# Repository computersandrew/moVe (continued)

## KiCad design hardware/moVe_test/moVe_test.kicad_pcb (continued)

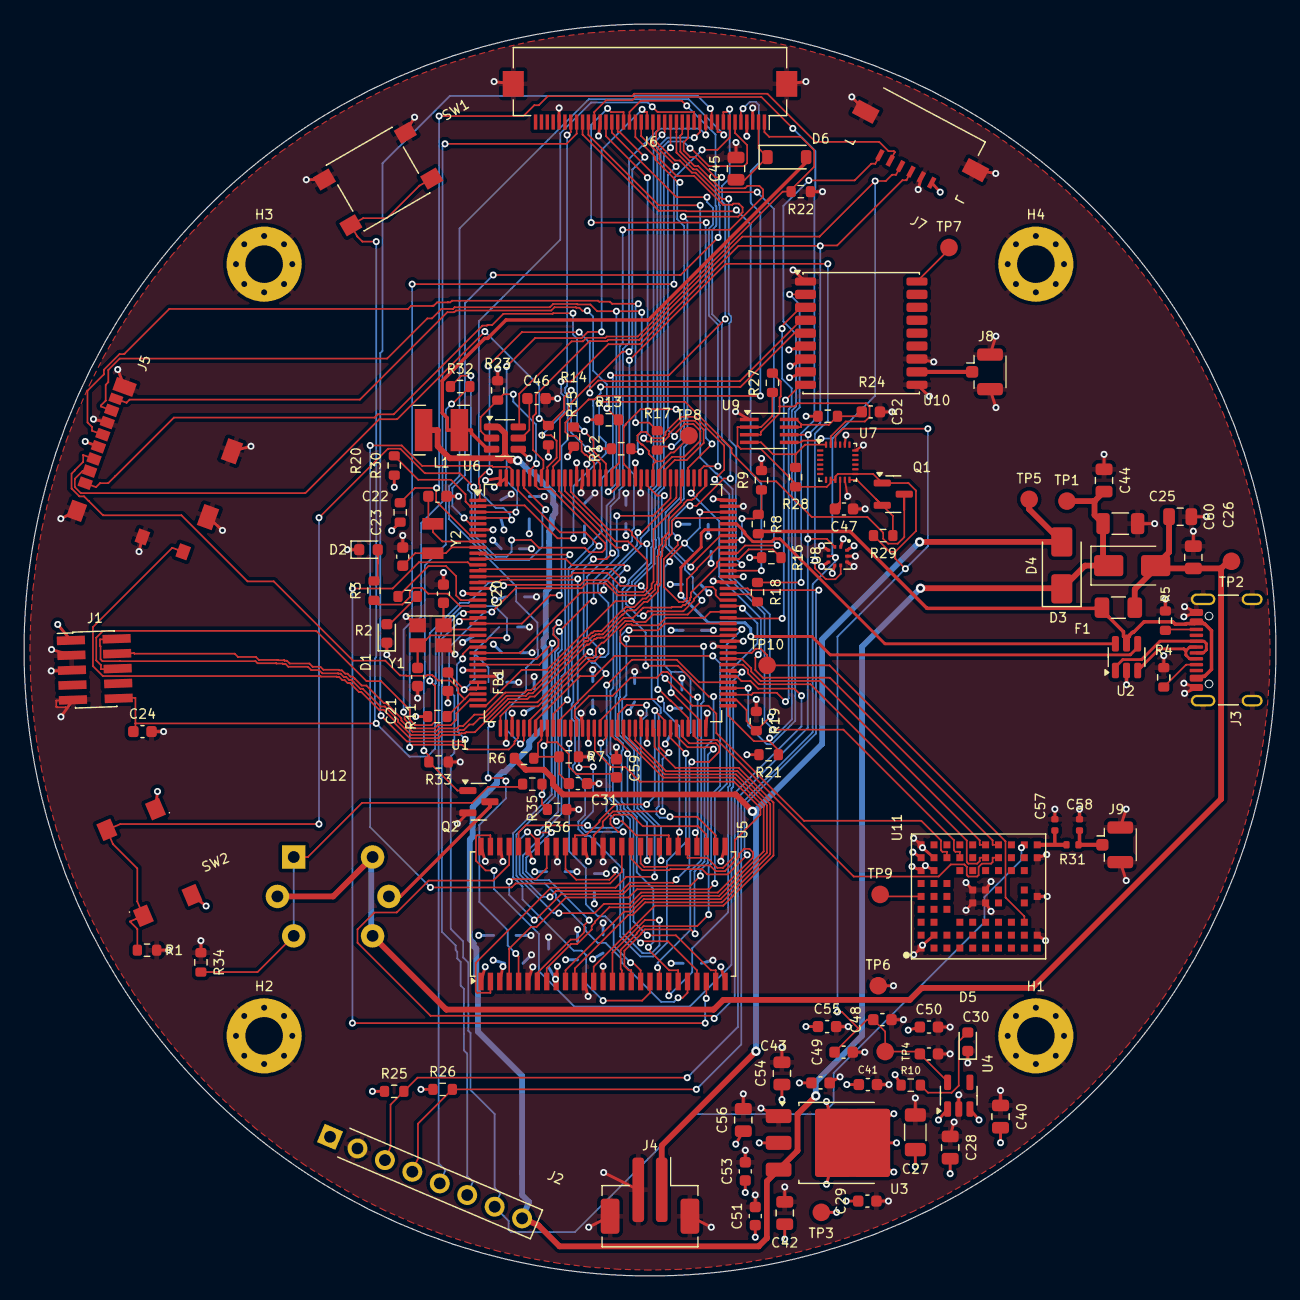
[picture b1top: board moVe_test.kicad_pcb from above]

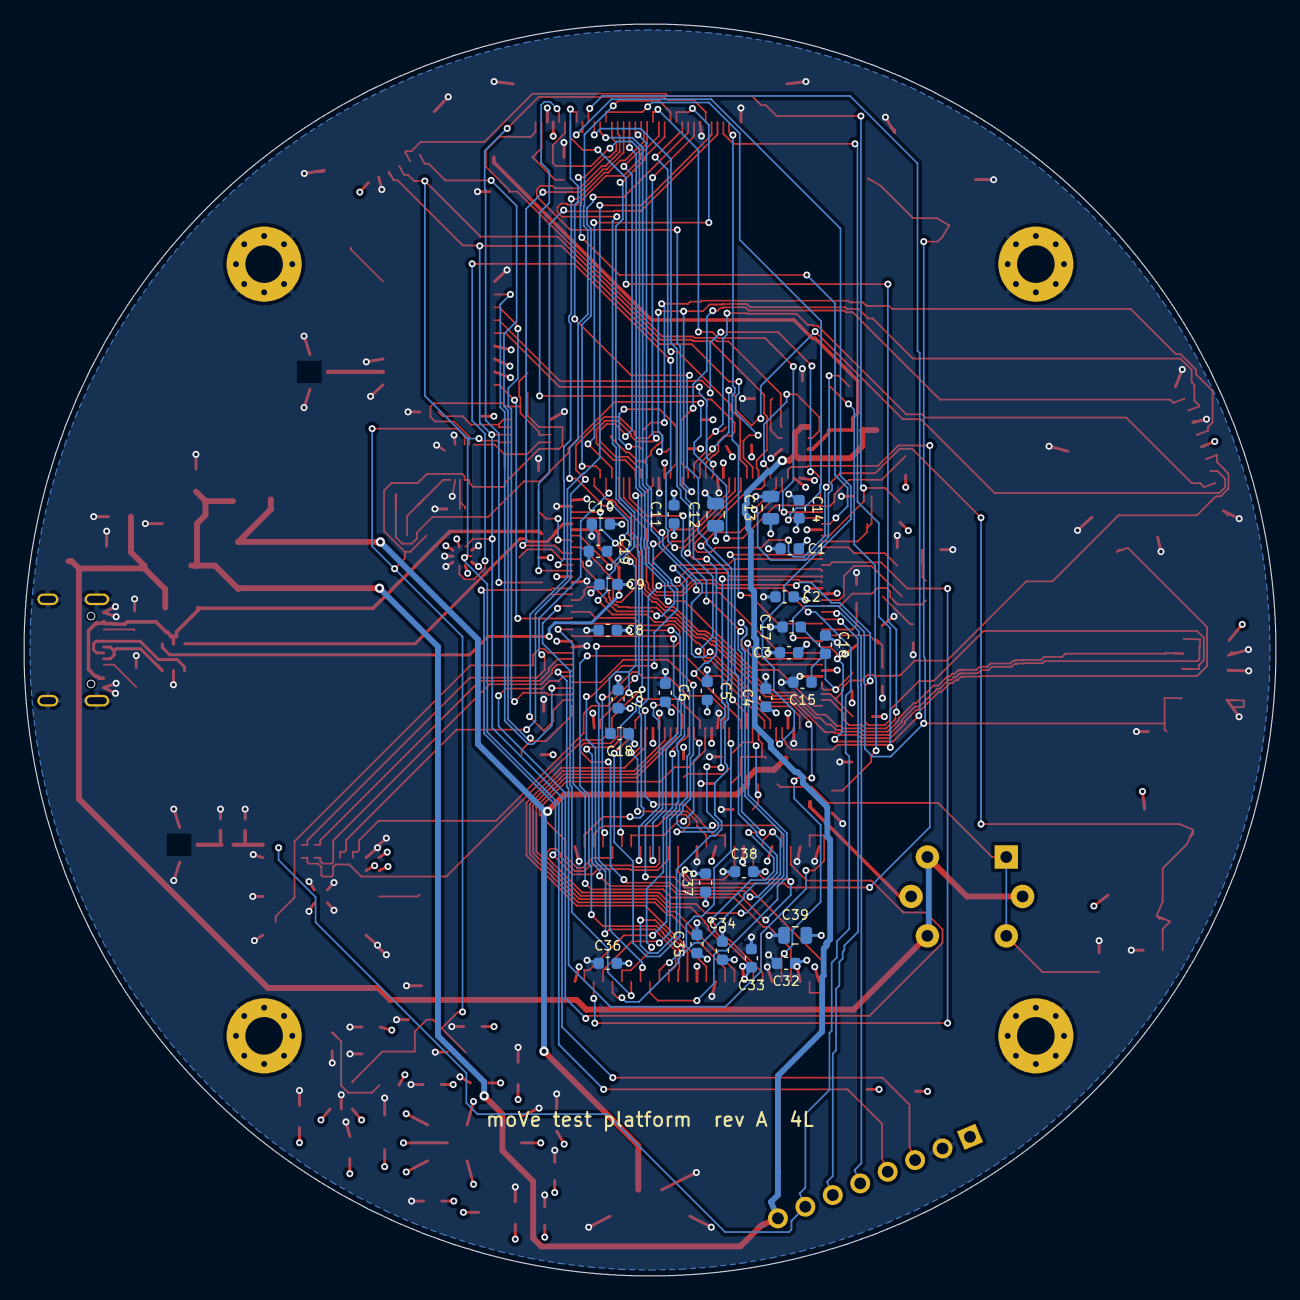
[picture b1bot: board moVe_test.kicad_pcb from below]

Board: 4 copper layers, 106.7 x 106.7 mm, 146 parts (27 on the bottom side), 149 nets.

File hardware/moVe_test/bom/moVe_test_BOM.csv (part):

Ref,Description,Qty per board,Unit price (USD),Per board (USD),MPN,Manufacturer,Category,Price basis,Link
U1,"MCU, Cortex-M7 550 MHz, LQFP-144",1,11.69,11.69,STM32H723ZGT6,STMicroelectronics,IC,parts.csv (Apr 2026),https://www.digikey.com/en/products/result?keywords=STM32H723ZGT6
U5,"64 Mb SDRAM x16, TSOP-II-54",1,3.13,3.13,AS4C4M16SA-7TCN,Alliance Memory,IC,parts.csv (Apr 2026),https://www.digikey.com/en/products/result?keywords=AS4C4M16SA-7TCN
U10,GNSS module,1,13.33,13.33,MAX-M10S-00B,u-blox,Module,parts.csv (Apr 2026),https://www.digikey.com/en/products/result?keywords=MAX-M10S-00B
U11,Bluetooth LE module,1,9.13,9.13,NORA-B261-00B,u-blox,Module,parts.csv (Apr 2026),https://www.digikey.com/en/products/result?keywords=NORA-B261-00B
U7,9-axis IMU,1,6.78,6.78,ICM-20948,TDK InvenSense,IC,parts.csv (Apr 2026),https://www.digikey.com/en/products/result?keywords=ICM-20948
U8,Barometric pressure sensor,1,3.15,3.15,BMP390,Bosch,IC,parts.csv (Apr 2026),https://www.digikey.com/en/products/result?keywords=BMP390
U12,CO gas sensor (aircraft build only),1,7.50,7.50,MQ-7B,Winsen,Sensor,parts.csv (Apr 2026),https://www.digikey.com/en/products/result?keywords=MQ-7B
U6,WLED backlight boost driver,1,2.15,2.15,TPS61165DBVR,Texas Instruments,IC,parts.csv (Apr 2026),https://www.digikey.com/en/products/result?keywords=TPS61165DBVR
U3,"3.3 V LDO, 800 mA, TO-252",1,0.96,0.96,TLV1117-33IKVURG3,Texas Instruments,IC,parts.csv (Apr 2026),https://www.digikey.com/en/products/result?keywords=TLV1117-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
U4,"1.8 V LDO, SOT-23-5",1,0.22,0.22,AP2112K-1.8TRG1,Diodes Inc.,IC,parts.csv (Apr 2026),https://www.digikey.com/en/products/result?keywords=AP2112K-1.8TRG1
U9,I2C level translator,1,0.69,0.69,PCA9306DCTR,Texas Instruments,IC,parts.csv (Apr 2026),https://www.digikey.com/en/products/result?keywords=PCA9306DCTR
U2,"USB ESD protection, SOT-23-6",1,0.36,0.36,USBLC6-2SC6,STMicroelectronics,IC,DigiKey US 1-pc (Nov 2026),https://www.digikey.com/en/products/result?keywords=USBLC6-2SC6
Q1,"N-MOSFET, SOT-23",1,0.20,0.20,BSS138,onsemi,Discrete,Est.,https://www.digikey.com/en/products/result?keywords=BSS138
Q2,"N-MOSFET, SOT-23 (MQ-7 heater)",1,0.30,0.30,AO3400A,Alpha & Omega,Discrete,Est.,https://www.digikey.com/en/products/result?keywords=AO3400A
Y1,"Crystal 25 MHz, 3225",1,0.65,0.65,ABM8-25.000MHZ-B2-T,Abracon,Discrete,"Farnell UK 1+ (£0.50, converted)",https://www.digikey.com/en/products/result?keywords=ABM8-25.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
Y2,"Crystal 32.768 kHz, 3215",1,0.59,0.59,ABS07-32.768KHZ-7-T,Abracon,Discrete,LCSC 1+ (Nov 2026),https://www.digikey.com/en/products/result?keywords=ABS07-32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
F1,"PTC fuse 1.1 A hold, 1812",1,0.37,0.37,MF-MSMF110-2,Bourns,Discrete,Findchips 1-pc (Nov 2026),https://www.digikey.com/en/products/result?keywords=MF-MSMF110-2
"D3,D4","Schottky 3 A 40 V, SMA",2,0.15,0.30,SS34,Generic,Discrete,Est.,https://www.digikey.com/en/products/result?keywords=SS34
D6,"Schottky 0.5 A 40 V, SOD-123",1,0.20,0.20,B0540W-7-F,Diodes Inc.,Discrete,Est.,https://www.digikey.com/en/products/result?keywords=B0540W-7-F
L1,"Power inductor 10 µH, 4018",1,0.37,0.37,SRN4018-100M,Bourns,Discrete,LCSC 1+ (Nov 2026),https://www.digikey.com/en/products/result?keywords=SRN4018-100M
FB1,"Ferrite bead 600 Ω @100 MHz, 0603",1,0.10,0.10,BLM18PG601SN1D,Murata,Discrete,Est.,https://www.digikey.com/en/products/result?keywords=BLM18PG601SN1D
D1,"LED green, 0603",1,0.10,0.10,,Generic,Discrete,Est.,https://www.digikey.com/en/products/result?keywords=LED+green+0603
D2,"LED blue, 0603",1,0.10,0.10,,Generic,Discrete,Est.,https://www.digikey.com/en/products/result?keywords=LED+blue+0603
D5,"LED red, 0603",1,0.10,0.10,,Generic,Discrete,Est.,https://www.digikey.com/en/products/result?keywords=LED+red+0603
J1,SWD header 2x5 1.27 mm,1,2.81,2.81,FTSH-105-01-L-DV-K-P,Samtec,Connector,parts.csv (Apr 2026),https://www.digikey.com/en/products/result?keywords=FTSH-105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
J2,Expansion header 1x8 2.54 mm,1,0.50,0.50,,Generic,Connector,Est.,https://www.digikey.com/en/products/result?keywords=1x8+pin+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
J3,USB-C receptacle,1,0.78,0.78,USB4105-GF-A-120,GCT,Connector,parts.csv (Apr 2026),https://www.digikey.com/en/products/result?keywords=USB4105-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
J4,Battery connector JST PH 2-pin SMD,1,0.43,0.43,B2B-PH-SM4-TB(LF)(SN),JST,Connector,LCSC 1+ (Nov 2026),https://www.digikey.com/en/products/result?keywords=B2B-PH-S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
J5,microSD socket,1,2.04,2.04,1040310811,Molex,Connector,parts.csv (Apr 2026),https://www.digikey.com/en/products/result?keywords=1040310811
J6,Display FPC 40-pin 0.5 mm,1,0.66,0.66,FH12-40S-0.5SH(55),Hirose,Connector,LCSC 1+ (Nov 2026),https://www.digikey.com/en/products/result?keywords=FH12-40S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
J7,Touch FFC 6-pin 1.0 mm,1,0.48,0.48,2005280060,Molex,Connector,TME 1+ (Nov 2026),https://www.digikey.com/en/products/result?keywords=2005280060
"J8,J9",U.FL antenna connector,2,1.20,2.40,U.FL-R-SMT-1(10),Hirose,Connector,parts.csv (Apr 2026),https://www.digikey.com/en/products/result?keywords=U.FL-R-S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
"SW1,SW2","Tactile switch (RESET, BOOT0)",2,0.32,0.64,PTS645SK43SMTR92 LFS,C&K,Connector,parts.csv (Apr 2026),https://www.digikey.com/en/products/result?keywords=PTS645SK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
"C1-C11,C14,C16,C17,C24,C31-C38,C41,C43,C47-C53,C55,C59","Cap 100 nF, 0603",34,0.02,0.68,,Generic,Passive,"Est. generic, 10+ cut tape",https://www.digikey.com/en/products/result?keywords=capacito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
"C12,C13,C44","Cap 4.7 µF, 0805",3,0.08,0.24,,Generic,Passive,"Est. generic, 10+ cut tape",https://www.digikey.com/en/products/result?keywords=capacito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
"C15,C29,C30","Cap 1 µF, 0603",3,0.04,0.12,,Generic,Passive,"Est. generic, 10+ cut tape",https://www.digikey.com/en/products/result?keywords=capacito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
"C18,C19","Cap 2.2 µF, 0603",2,0.05,0.10,,Generic,Passive,"Est. generic, 10+ cut tape",https://www.digikey.com/en/products/result?keywords=capacito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
"C20,C21","Cap 12 pF C0G, 0603",2,0.03,0.06,,Generic,Passive,"Est. generic, 10+ cut tape",https://www.digikey.com/en/products/result?keywords=capacito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
"C22,C23","Cap 10 pF C0G, 0603",2,0.03,0.06,,Generic,Passive,"Est. generic, 10+ cut tape",https://www.digikey.com/en/products/result?keywords=capacito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
C25,"Cap 10 µF, 1206",1,0.20,0.20,,Generic,Passive,"Est. generic, 10+ cut tape",https://www.digikey.com/en/products/result?keywords=capacito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
"C26,C28,C39,C40,C42,C54,C56,C60","Cap 10 µF, 0805",8,0.10,0.80,,Generic,Passive,"Est. generic, 10+ cut tape",https://www.digikey.com/en/products/result?keywords=capacito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
C27,"Cap 22 µF, 1206",1,0.25,0.25,,Generic,Passive,"Est. generic, 10+ cut tape",https://www.digikey.com/en/products/result?keywords=capacito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
C45,"Cap 1 µF 50 V, 0805",1,0.10,0.10,,Generic,Passive,"Est. generic, 10+ cut tape",https://www.digikey.com/en/products/result?keywords=capacito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
C46,"Cap 220 nF, 0603",1,0.03,0.03,,Generic,Passive,"Est. generic, 10+ cut tape",https://www.digikey.com/en/products/result?keywords=capacito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
"C57,C58",Cap 0402 — not fitted (RF match),2,0.00,0.00,,DNP,Passive,DNP,https://www.digikey.com/en/products/result?keywords=capacitor+0402
"R1,R8,R11-R16,R19-R21,R29,R30,R34,R35","Res 10 kΩ, 0603",15,0.02,0.30,,Generic,Passive,"Est. generic, 10+ cut tape",https://www.digikey.com/en/products/result?keywords=resistor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
R25-R28,"Res 4.7 kΩ, 0603",4,0.02,0.08,,Generic,Passive,"Est. generic, 10+ cut tape",https://www.digikey.com/en/products/result?keywords=resistor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
"R6,R23,R33","Res 100 kΩ, 0603",3,0.02,0.06,,Generic,Passive,"Est. generic, 10+ cut tape",https://www.digikey.com/en/products/result?keywords=resistor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
"R2,R3","Res 1 kΩ, 0603",2,0.02,0.04,,Generic,Passive,"Est. generic, 10+ cut tape",https://www.digikey.com/en/products/result?keywords=resistor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
"R4,R5","Res 5.1 kΩ, 0603 (USB-C CC)",2,0.02,0.04,,Generic,Passive,"Est. generic, 10+ cut tape",https://www.digikey.com/en/products/result?keywords=resistor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
"R9,R36","Res 20 kΩ, 0603",2,0.02,0.04,,Generic,Passive,"Est. generic, 10+ cut tape",https://www.digikey.com/en/products/result?keywords=resistor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
R7,"Res 33 kΩ, 0603",1,0.02,0.02,,Generic,Passive,"Est. generic, 10+ cut tape",https://www.digikey.com/en/products/result?keywords=resistor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

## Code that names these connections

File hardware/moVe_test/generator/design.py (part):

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    MCU[pin] = net

for p, n in {
    "PA0": "SDMMC2_CMD", "PA1": "LTDC_R2", "PA2": "LTDC_R1", "PA3": "LTDC_B2", "PA4": "LTDC_VSYNC",
    "PA5": "LTDC_R4", "PA6": "LTDC_G2", "PA7": "FMC_SDNWE", "PA8": "LTDC_B3", "PA9": "VBUS_SENSE",
    "PA10": "LTDC_B1", "PA11": "USB_DM", "PA12": "USB_DP", "PA13": "SWDIO", "PA14": "SWCLK", "PA15": "LTDC_B6",
    "PB0": "LTDC_R3", "PB1": "LTDC_R6", "PB3": "SWO", "PB4": "BARO_INT", "PB5": "LTDC_B5",
    "PB6": "I2C1_SCL", "PB7": "I2C1_SDA", "PB8": "BL_PWM", "PB9": "MQ7_HEAT", "PB10": "LTDC_G4",
    "PB11": "BLE_UART_RX", "PB12": "TOUCH_RST_N", "PB13": "LCD_STBYB", "PB14": "GPS_UART_TX", "PB15": "GPS_UART_RX",
    "PC0": "LTDC_R5", "PC1": "LTDC_G5", "PC2_C": "FMC_SDNE0", "PC3_C": "FMC_SDCKE0", "PC4": "VBAT_SENSE",
    "PC5": "MQ7_ADC", "PC6": "LTDC_HSYNC", "PC7": "LTDC_G6", "PC8": "SD_DETECT", "PC9": "LTDC_G3",
    "PC10": "BLE_UART_TX", "PC11": "LTDC_B4", "PC12": "BLE_WAKE", "PC13": "TOUCH_INT_N",
    "PC14": "OSC32_IN", "PC15": "OSC32_OUT",
    "PD0": "FMC_D2", "PD1": "FMC_D3", "PD2": "LTDC_B7", "PD3": "LTDC_G7", "PD4": "BLE_SW1", "PD5": "BLE_SW2",
    "PD6": "SDMMC2_CK", "PD8": "FMC_D13", "PD9": "FMC_D14", "PD10": "FMC_D15",
    "PD11": "BLE_CTS", "PD12": "BLE_RTS", "PD13": "BLE_RESET_N", "PD14": "FMC_D0", "PD15": "FMC_D1",
    "PE0": "FMC_NBL0", "PE1": "FMC_NBL1", "PE2": "GPS_TIMEPULSE", "PE3": "IMU_INT", "PE4": "LTDC_B0",
    "PE5": "LTDC_G0", "PE6": "LTDC_G1",
    "PF0": "FMC_A0", "PF1": "FMC_A1", "PF2": "FMC_A2", "PF3": "FMC_A3", "PF4": "FMC_A4", "PF5": "FMC_A5",
    "PF6": "LED1", "PF7": "LED2", "PF8": "EXP_PF8", "PF9": "EXP_PF9", "PF10": "LTDC_DE", "PF11": "FMC_SDNRAS",
    "PF12": "FMC_A6", "PF13": "FMC_A7", "PF14": "FMC_A8", "PF15": "FMC_A9",
    "PG0": "FMC_A10", "PG1": "FMC_A11", "PG2": "FMC_A12", "PG3": "GPS_RESET_N", "PG4": "FMC_BA0", "PG5": "FMC_BA1",
    "PG6": "LTDC_R7", "PG7": "LTDC_CLK", "PG8": "FMC_SDCLK", "PG9": "SDMMC2_D0", "PG10": "SDMMC2_D1",
    "PG11": "SDMMC2_D2", "PG12": "SDMMC2_D3", "PG13": "LTDC_R0", "PG14": "GPS_EXTINT", "PG15": "FMC_SDNCAS",
    "PH0": "HSE_IN", "PH1": "HSE_OUT", "PDR_ON": "+3V3", "NRST": "NRST", "BOOT0": "BOOT0",
    "VBAT": "+3V3", "VDD": "+3V3", "VSS": "GND", "VSSA": "GND", "VDDA": "VDDA", "VREF+": "VDDA",
    "VDD33USB": "+3V3", "VCAP": "VCAP",
}.items():
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     "7": "SDMMC2_D0", "8": "SDMMC2_D1", "9": "GND", "10": "SD_DETECT", "11": "GND"}, mpn="1040310811")
for n in ("SDMMC2_CMD", "SDMMC2_D0", "SDMMC2_D1", "SDMMC2_D2", "SDMMC2_D3", "SD_DETECT"):
    R(S, "10k", "+3V3", n)
R(S, "22R", "SDMMC2_CK", "SDMMC2_CK_SD").pins = {"1": "SDMMC2_CK", "2": "SDMMC2_CK_SD"}
# route clock through series resistor at the socket
for c in COMPS:
    if c.lib_id == "Connector:Micro_SD_Card_Det2":
        c.pins["5"] = "SDMMC2_CK_SD"
C(S, "10u", "+3V3", fp=FP_C0805)
C(S, "100n", "+3V3")

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
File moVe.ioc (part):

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Mcu.Name=STM32H723ZGTx
Mcu.Package=LQFP144
Mcu.UserName=STM32H723ZGTx
PA0.Mode=SD_4_bits_Wide_bus
PA0.Signal=SDMMC2_CMD
PA1.Mode=RGB888
PA1.Signal=LTDC_R2
PA10.Mode=RGB888
PA10.Signal=LTDC_B1
PA11.Mode=Device_Only_FS
PA11.Signal=USB_OTG_HS_DM
PA12.Mode=Device_Only_FS
PA12.Signal=USB_OTG_HS_DP
PA13(JTMS/SWDIO).Mode=Serial_Wire
PA13(JTMS/SWDIO).Signal=DEBUG_JTMS-SWDIO
PA14(JTCK/SWCLK).Mode=Serial_Wire
PA14(JTCK/SWCLK).Signal=DEBUG_JTCK-SWCLK
PA15(JTDI).Mode=RGB888
PA15(JTDI).Signal=LTDC_B6
PA2.Mode=RGB888
PA2.Signal=LTDC_R1
PA3.Mode=RGB888
PA3.Signal=LTDC_B2
PA4.Mode=RGB888
PA4.Signal=LTDC_VSYNC
PA5.Mode=RGB888
PA5.Signal=LTDC_R4
PA6.Mode=RGB888
PA6.Signal=LTDC_G2
PA7.Signal=FMC_SDNWE
PA8.Mode=RGB888
PA8.Signal=LTDC_B3
PB0.Mode=RGB888
PB0.Signal=LTDC_R3
PB1.Mode=RGB888
PB1.Signal=LTDC_R6
PB10.Mode=RGB888
PB10.Signal=LTDC_G4
PB11.Mode=Asynchronous
PB11.Signal=USART3_RX
PB14.Mode=Asynchronous
PB14.Signal=USART1_TX
PB15.Mode=Asynchronous
PB15.Signal=USART1_RX
PB5.Mode=RGB888
PB5.Signal=LTDC_B5
PB6.Mode=I2C
PB6.Signal=I2C1_SCL
PB7.Mode=I2C
PB7.Signal=I2C1_SDA
PC0.Mode=RGB888
PC0.Signal=LTDC_R5
PC1.Mode=RGB888
PC1.Signal=LTDC_G5
PC10.Mode=Asynchronous
PC10.Signal=USART3_TX
PC11.Mode=RGB888
PC11.Signal=LTDC_B4
PC2_C.Mode=SdramChipSelect1_1
PC2_C.Signal=FMC_SDNE0
PC3_C.Mode=SdramChipSelect1_1
PC3_C.Signal=FMC_SDCKE0
PC4.Signal=ADCx_INP4
PC6.Mode=RGB888
PC6.Signal=LTDC_HSYNC
PC7.Mode=RGB888
PC7.Signal=LTDC_G6
PC9.Mode=RGB888
PC9.Signal=LTDC_G3
PD0.Signal=FMC_D2_DA2
PD1.Signal=FMC_D3_DA3
PD10.Signal=FMC_D15_DA15
PD14.Signal=FMC_D0_DA0
PD15.Signal=FMC_D1_DA1
PD2.Mode=RGB888
PD2.Signal=LTDC_B7
PD3.Mode=RGB888
PD3.Signal=LTDC_G7
PD6.Mode=SD_4_bits_Wide_bus
PD6.Signal=SDMMC2_CK
PD8.Signal=FMC_D13_DA13
PD9.Signal=FMC_D14_DA14
PE0.Signal=FMC_NBL0
PE1.Signal=FMC_NBL1
PE10.Signal=FMC_D7_DA7
PE11.Signal=FMC_D8_DA8
PE12.Signal=FMC_D9_DA9
PE13.Signal=FMC_D10_DA10
PE14.Signal=FMC_D11_DA11
PE15.Signal=FMC_D12_DA12
PE4.Mode=RGB888
PE4.Signal=LTDC_B0
PE5.Mode=RGB888
PE5.Signal=LTDC_G0
PE6.Mode=RGB888
PE6.Signal=LTDC_G1
PE7.Signal=FMC_D4_DA4
PE8.Signal=FMC_D5_DA5
PE9.Signal=FMC_D6_DA6
PF0.Signal=FMC_A0
PF1.Signal=FMC_A1
PF10.Mode=RGB888
PF10.Signal=LTDC_DE
PF11.Signal=FMC_SDNRAS
PF12.Signal=FMC_A6
PF13.Signal=FMC_A7
PF14.Signal=FMC_A8
PF15.Signal=FMC_A9
PF2.Signal=FMC_A2
PF3.Signal=FMC_A3
PF4.Signal=FMC_A4
PF5.Signal=FMC_A5
PG0.Signal=FMC_A10
PG1.Signal=FMC_A11
PG10.Mode=SD_4_bits_Wide_bus
PG10.Signal=SDMMC2_D1
PG11.Mode=SD_4_bits_Wide_bus
PG11.Signal=SDMMC2_D2
PG12.Mode=SD_4_bits_Wide_bus
PG12.Signal=SDMMC2_D3
PG13.Mode=RGB888
PG13.Signal=LTDC_R0
PG15.Signal=FMC_SDNCAS
PG2.Signal=FMC_A12
PG4.Signal=FMC_A14_BA0
PG5.Signal=FMC_A15_BA1
PG6.Mode=RGB888
PG6.Signal=LTDC_R7
PG7.Mode=RGB888
PG7.Signal=LTDC_CLK
PG8.Signal=FMC_SDCLK
PG9.Mode=SD_4_bits_Wide_bus
PG9.Signal=SDMMC2_D0
RCC.SYSCLKFreq_VALUE=64000000
board=custom

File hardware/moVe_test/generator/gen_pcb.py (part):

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put(NORA, 178.0, 121.0, -90)
put(BLE_UFL, 189.6, 116.6, 0)
R_MATCH = one(lambda c: c.value == "0R")
C_SH1 = one(lambda c: c.dnp and "BLE_ANT" in c.pins.values())
C_SH2 = one(lambda c: c.dnp and "BLE_ANT_M" in c.pins.values())
put(R_MATCH, 186.0, 116.6, 0)
put(C_SH1, 184.5, 114.9, 90, check=False)
put(C_SH2, 186.6, 114.9, 90, check=False)
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put(IMU, 166.0, 84.0, 0)
put(BARO, 166.0, 92.0, 0)
put(HSE, 131.3, 98.75, 180)
C_HSE_IN = one(lambda c: c.value == "12p" and "HSE_IN" in c.pins.values())
C_HSE_OUT = one(lambda c: c.value == "12p" and "HSE_OUT" in c.pins.values())
put(C_HSE_IN, 132.4, 95.2, 90, check=False)
put(C_HSE_OUT, 130.2, 102.3, 270, check=False)
put(LSE, 131.5, 90.5, 90)
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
